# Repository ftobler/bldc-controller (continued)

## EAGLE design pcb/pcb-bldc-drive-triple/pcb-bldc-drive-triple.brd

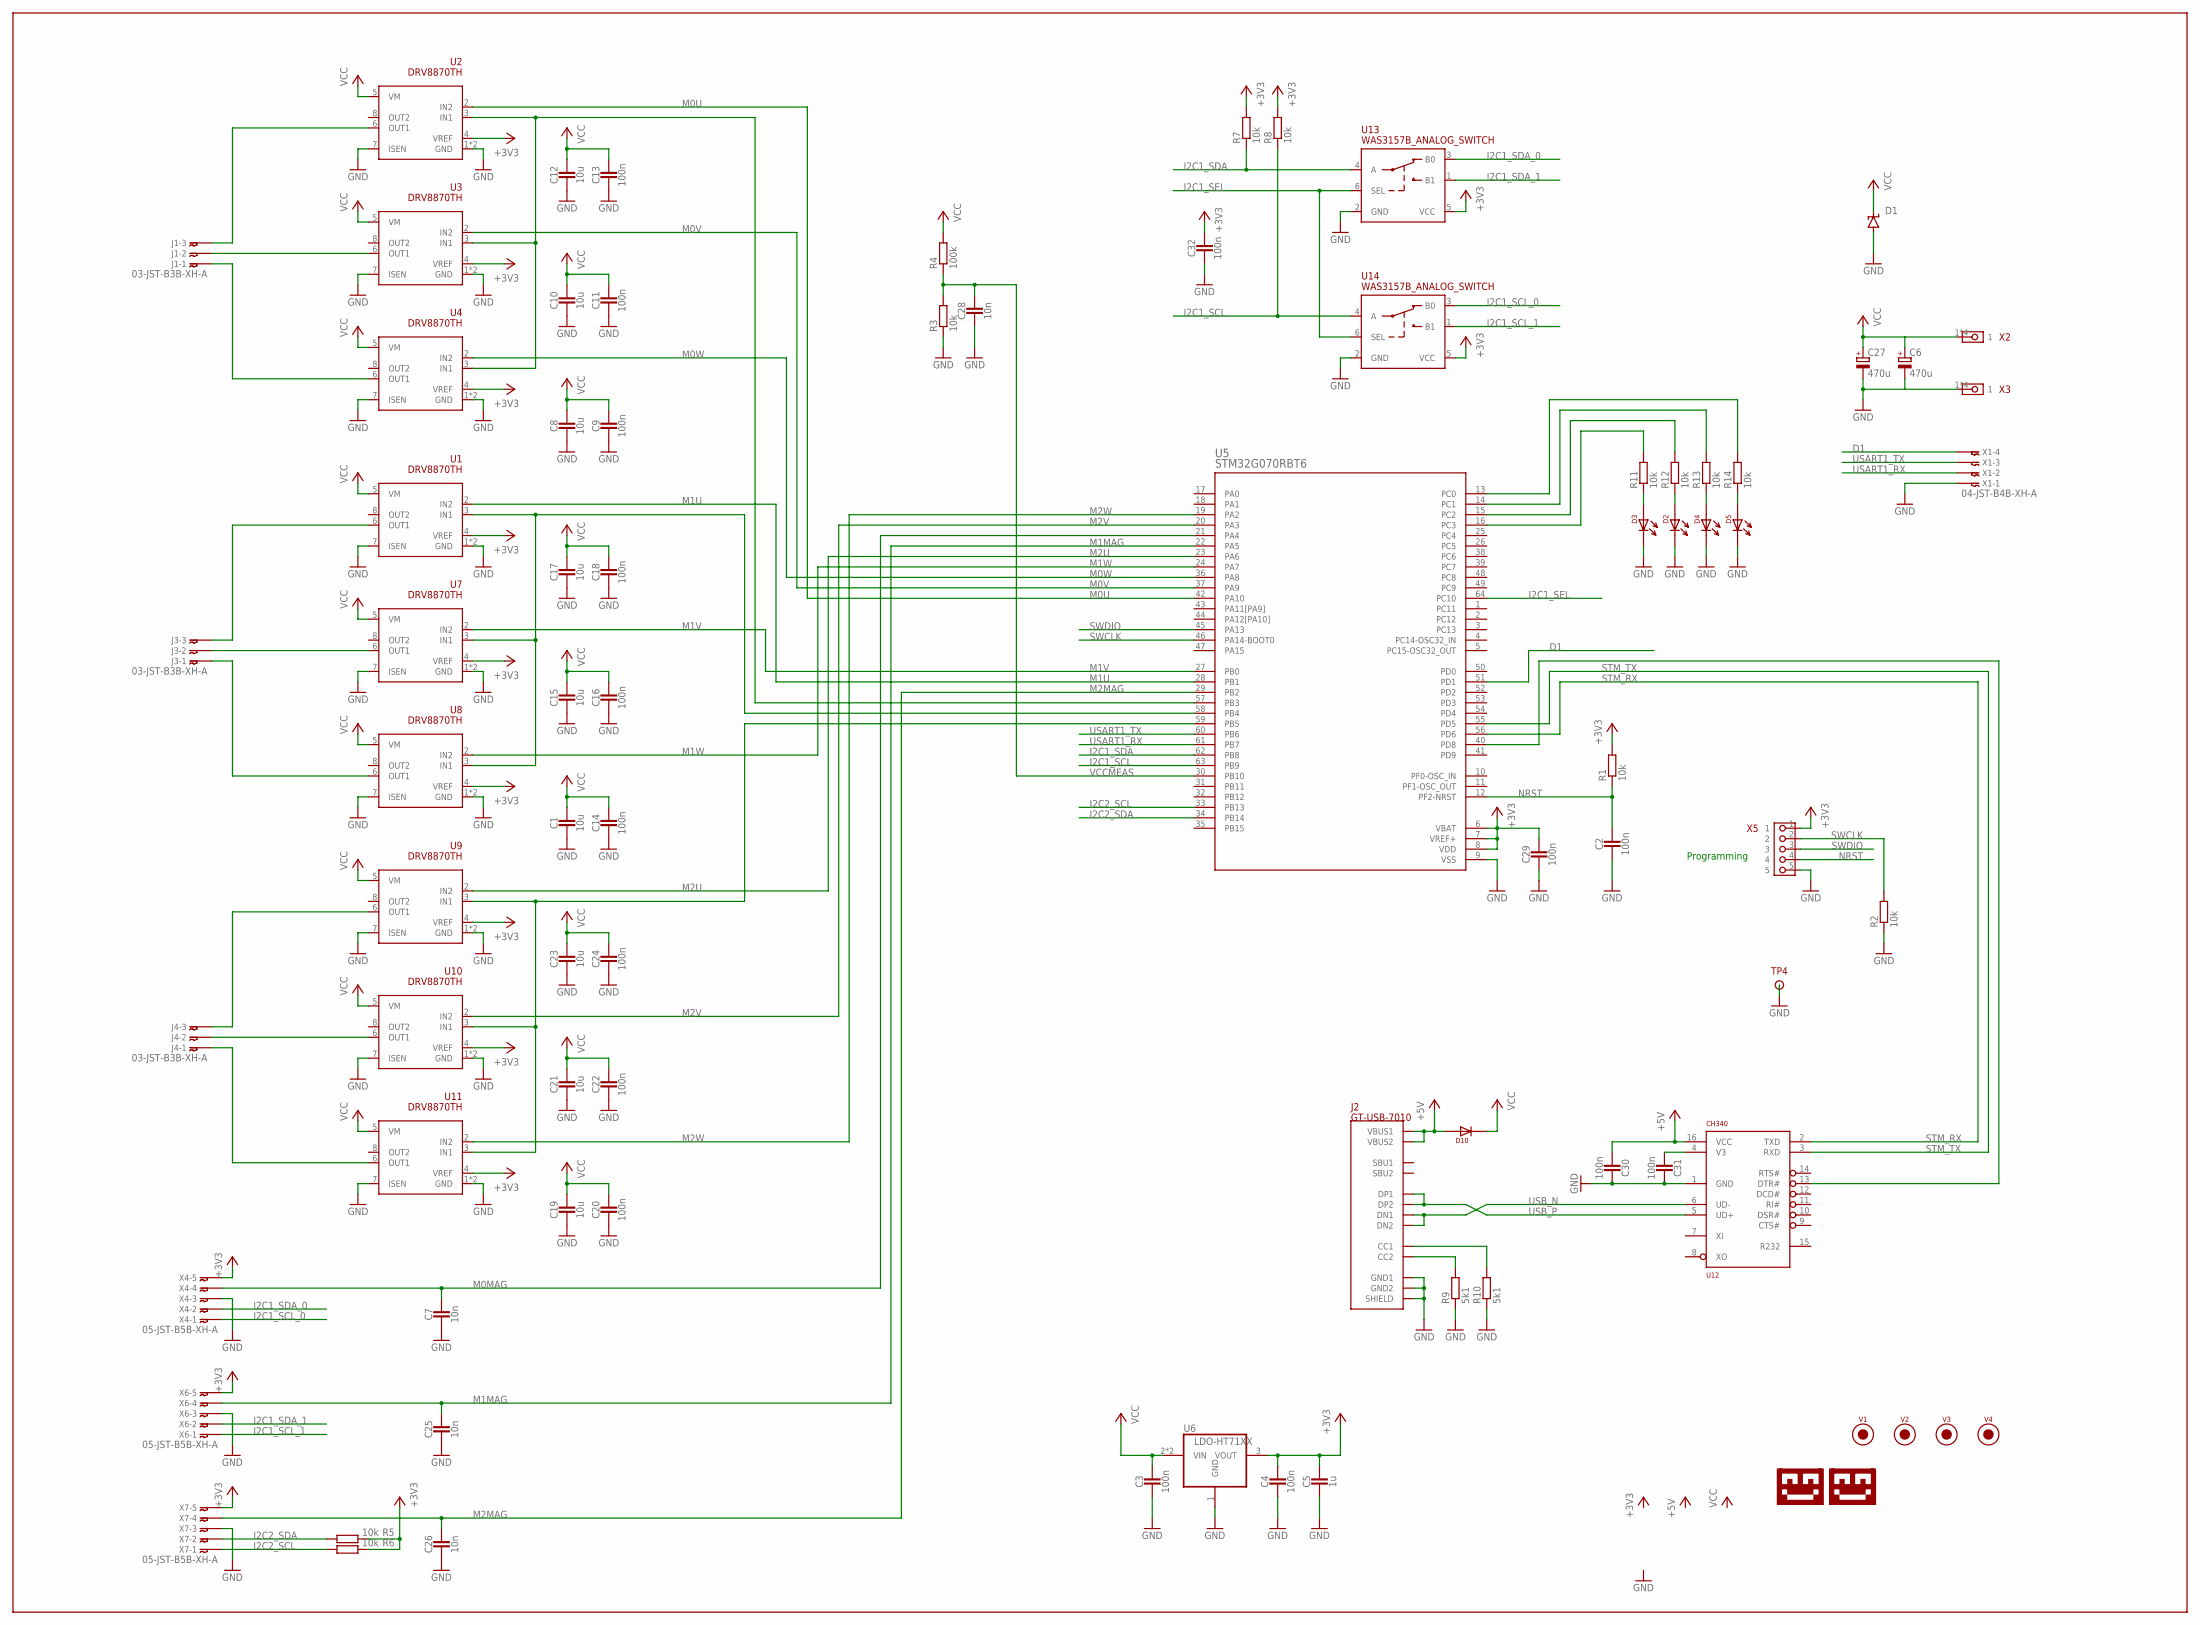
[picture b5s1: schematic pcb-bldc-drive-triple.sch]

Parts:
C1, C8, C10, C12, C15, C17, C19, C21, C23: 10u; 1206_CAP
C2, C3, C4, C9, C11, C13, C14, C16, C18, C20, C22, C24, C29, C30, C31, C32: 100n; 0603_CAP
C5: 1u; 0603_CAP
C6, C27: 470u; 153CLV-1010
C7, C25, C26, C28: 10n; 0603_CAP
D1: SUPPRESSOR-SMBJ; SMBJ
D2, D3, D4, D5: LED-0805; 0805-DOT
D10: DIODE-1206; 1206-DOT
J1, J3, J4: 03-JST-B3B-XH-A; B3B-XH
J2: GT-USB-7010
R1, R2, R3, R5, R6, R7, R8, R11, R12, R13, R14: 10k; 0603-RES
R4: 100k; 0603-RES
R9, R10: 5k1; 0603-RES
TP4: TESTPIN1MM; PIN-SMD-1X1-TEST_1M0
U1, U2, U3, U4, U7, U8, U9, U10, U11: DRV8870TH; SOIC-8-THERM
U5: STM32G070RBT6; LQFP-64
U6: LDO-HT71XX; SOT-89
U12: CH340; SOIC-16
U13, U14: WAS3157B_ANALOG_SWITCH; SOT323-6
U$1: LOGO-TOBENG-1MM-FINISH; TOBENG-1MM-FINISH
U$2: LOGO-TOBENG-4MM-MASK; TOBENG-4MM-MASK
V1, V2, V3, V4: FIDUCIAL2MM; FIDUCIAL_2MM
X1: 04-JST-B4B-XH-A; B4B-XH
X2, X3: PIN_1X1WELDINGTERMINAL; XFCNTS34031
X4, X6, X7: 05-JST-B5B-XH-A; B5B-XH
X5: PIN_5X1HD; PIN_5X1_HD

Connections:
+3V3: C4.1, C5.1, C29.1, C32.1, R1.2, R5.1, R6.1, R7.2, R8.2, U1.4 (VREF), U2.4 (VREF), U3.4 (VREF), U4.4 (VREF), U5.6 (VBAT), U5.7 (VREF+), U5.8 (VDD), U6.3 (VOUT), U7.4 (VREF), U8.4 (VREF), U9.4 (VREF), U10.4 (VREF), U11.4 (VREF), U13.5 (VCC), U14.5 (VCC), X4.P$5, X5.1, X6.P$5, X7.P$5
+5V: C30.2, D10.1, J2.A4B9 (VBUS1), J2.B4A9 (VBUS2), U12.16 (VCC)
D1: U5.51 (PD1), X1.P$4
GND: C1.2, C2.2, C3.2, C4.2, C5.2, C6.-, C7.2, C8.2, C9.2, C10.2, C11.2, C12.2, C13.2, C14.2, C15.2, C16.2, C17.2, C18.2, C19.2, C20.2, C21.2, C22.2, C23.2, C24.2, C25.2, C26.2, C27.-, C28.2, C29.2, C30.1, C31.1, C32.2, D1.A, D2.2, D3.2, D4.2, D5.2, J2.13 (SHIELD), J2.14 (SHIELD), J2.15 (SHIELD), J2.16 (SHIELD), J2.A1B12 (GND1), J2.B1A12 (GND2), R2.1, R3.1, R9.1, R10.1, TP4.1, U1.1 (GND), U1.7 (ISEN), U1.9 (GND), U2.1 (GND), U2.7 (ISEN), U2.9 (GND), U3.1 (GND), U3.7 (ISEN), U3.9 (GND), U4.1 (GND), U4.7 (ISEN), U4.9 (GND), U5.9 (VSS), U6.1 (GND), U7.1 (GND), U7.7 (ISEN), U7.9 (GND), U8.1 (GND), U8.7 (ISEN), U8.9 (GND), U9.1 (GND), U9.7 (ISEN), U9.9 (GND), U10.1 (GND), U10.7 (ISEN), U10.9 (GND), U11.1 (GND), U11.7 (ISEN), U11.9 (GND), U12.1 (GND), U13.2 (GND), U14.2 (GND), X1.P$1, X3.1, X3.2, X3.3, X3.4, X4.P$3, X5.5, X6.P$3, X7.P$3
I2C1_SCL: R8.1, U5.63 (PB9), U14.4 (A)
I2C1_SCL_0: U14.3 (B0), X4.P$1
I2C1_SCL_1: U14.1 (B1), X6.P$1
I2C1_SDA: R7.1, U5.62 (PB8), U13.4 (A)
I2C1_SDA_0: U13.3 (B0), X4.P$2
I2C1_SDA_1: U13.1 (B1), X6.P$2
I2C1_SEL: U5.64 (PC10), U13.6 (SEL), U14.6 (SEL)
I2C2_SCL: R6.2, U5.33 (PB13), X7.P$1
I2C2_SDA: R5.2, U5.34 (PB14), X7.P$2
M0MAG: C7.1, U5.21 (PA4), X4.P$4
M0U: U2.2 (IN2), U5.42 (PA10)
M0V: U3.2 (IN2), U5.37 (PA9)
M0W: U4.2 (IN2), U5.36 (PA8)
M1MAG: C25.1, U5.22 (PA5), X6.P$4
M1U: U1.2 (IN2), U5.28 (PB1)
M1V: U5.27 (PB0), U7.2 (IN2)
M1W: U5.24 (PA7), U8.2 (IN2)
M2MAG: C26.1, U5.29 (PB2), X7.P$4
M2U: U5.23 (PA6), U9.2 (IN2)
M2V: U5.20 (PA3), U10.2 (IN2)
M2W: U5.19 (PA2), U11.2 (IN2)
unnamed: J2.B5 (CC2), R9.2
unnamed: J2.A5 (CC1), R10.2
unnamed: J1.P$2, U3.6 (OUT1)
unnamed: J1.P$3, U2.6 (OUT1)
unnamed: C31.2, U12.4 (V3)
unnamed: J3.P$3, U1.6 (OUT1)
unnamed: J1.P$1, U4.6 (OUT1)
unnamed: D3.1, R11.1
unnamed: J3.P$2, U7.6 (OUT1)
unnamed: J3.P$1, U8.6 (OUT1)
unnamed: U5.59 (PB5), U9.3 (IN1), U10.3 (IN1), U11.3 (IN1)
unnamed: U1.3 (IN1), U5.58 (PB4), U7.3 (IN1), U8.3 (IN1)
unnamed: J4.P$3, U9.6 (OUT1)
unnamed: U2.3 (IN1), U3.3 (IN1), U4.3 (IN1), U5.57 (PB3)
unnamed: J4.P$2, U10.6 (OUT1)
unnamed: J4.P$1, U11.6 (OUT1)
unnamed: D2.1, R12.1
unnamed: D4.1, R13.1
unnamed: D5.1, R14.1
unnamed: R14.2, U5.13 (PC0)
unnamed: R13.2, U5.14 (PC1)
unnamed: R12.2, U5.15 (PC2)
unnamed: R11.2, U5.16 (PC3)
unnamed: U5.40 (PD8), U12.13 (DTR#)
NRST: C2.1, R1.1, U5.12 (PF2-NRST), X5.4
STM_RX: U5.56 (PD6), U12.2 (TXD)
STM_TX: U5.55 (PD5), U12.3 (RXD)
SWCLK: R2.2, U5.46 (PA14-BOOT0), X5.2
SWDIO: U5.45 (PA13), X5.3
USART1_RX: U5.61 (PB7), X1.P$2
USART1_TX: U5.60 (PB6), X1.P$3
USB_N: J2.A7 (DN1), J2.B7 (DN2), U12.6 (UD-)
USB_P: J2.A6 (DP1), J2.B6 (DP2), U12.5 (UD+)
VCC: C1.1, C3.1, C6.+, C8.1, C9.1, C10.1, C11.1, C12.1, C13.1, C14.1, C15.1, C16.1, C17.1, C18.1, C19.1, C20.1, C21.1, C22.1, C23.1, C24.1, C27.+, D1.C, D10.2, R4.2, U1.5 (VM), U2.5 (VM), U3.5 (VM), U4.5 (VM), U6.2 (VIN), U6.2@1 (VIN), U7.5 (VM), U8.5 (VM), U9.5 (VM), U10.5 (VM), U11.5 (VM), X2.1, X2.2, X2.3, X2.4
VCCMEAS: C28.1, R3.2, R4.1, U5.30 (PB10)

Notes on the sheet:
Programming

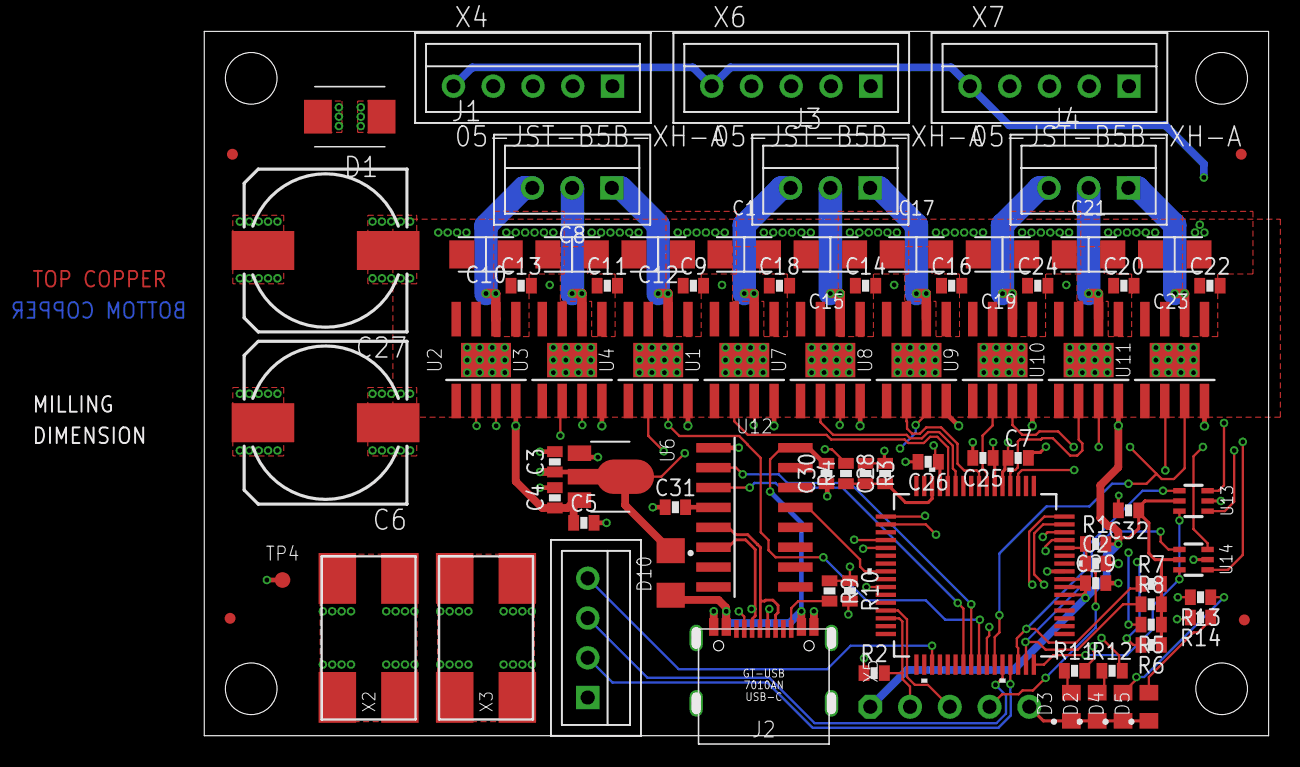
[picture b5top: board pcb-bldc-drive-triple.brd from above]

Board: 4 copper layers, 68.0 x 45.0 mm, 84 parts (1 on the bottom side), 60 nets.

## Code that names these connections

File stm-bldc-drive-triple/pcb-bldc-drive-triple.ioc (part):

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Mcu.Name=STM32G070RBTx
Mcu.Package=LQFP64
Mcu.UserName=STM32G070RBTx
PA10.Signal=S_TIM1_CH3
PA11\ [PA9].Signal=S_TIM1_CH4
PA13.Mode=Serial_Wire
PA13.Signal=SYS_SWDIO
PA14-BOOT0.Mode=Serial_Wire
PA14-BOOT0.Signal=SYS_SWCLK
PA2.Signal=S_TIM15_CH1
PA3.Signal=S_TIM15_CH2
PA4.Mode=IN4
PA4.Signal=ADC1_IN4
PA5.Mode=IN5
PA5.Signal=ADC1_IN5
PA6.Signal=S_TIM3_CH1
PA7.Signal=S_TIM3_CH2
PA8.Signal=S_TIM1_CH1
PA9.Signal=S_TIM1_CH2
PB0.Signal=S_TIM3_CH3
PB1.Signal=S_TIM3_CH4
PB10.Mode=IN11
PB10.Signal=ADC1_IN11
PB13.Mode=I2C
PB13.Signal=I2C2_SCL
PB14.Mode=I2C
PB14.Signal=I2C2_SDA
PB2.Mode=IN10
PB2.Signal=ADC1_IN10
PB3.GPIOParameters=GPIO_Label
PB3.GPIO_Label=ENABLE_M3
PB3.Signal=GPIO_Output
PB4.GPIOParameters=GPIO_Label
PB4.GPIO_Label=ENABLE_M2
PB4.Signal=GPIO_Output
PB5.GPIOParameters=GPIO_Label
PB5.GPIO_Label=ENABLE_M1
PB5.Signal=GPIO_Output
PB6.Mode=Asynchronous
PB6.Signal=USART1_TX
PB7.Mode=Asynchronous
PB7.Signal=USART1_RX
PB8.Mode=I2C
PB8.Signal=I2C1_SCL
PB9.Mode=I2C
PB9.Signal=I2C1_SDA
PC0.GPIOParameters=GPIO_Label
PC0.GPIO_Label=LED1
PC0.Signal=GPIO_Output
PC1.GPIOParameters=GPIO_Label
PC1.GPIO_Label=LED2
PC1.Signal=GPIO_Output
PC10.GPIOParameters=GPIO_Label
PC10.GPIO_Label=I2C1_SEL
PC10.Signal=GPIO_Output
PC2.GPIOParameters=GPIO_Label
PC2.GPIO_Label=LED3
PC2.Signal=GPIO_Output
PC3.GPIOParameters=GPIO_Label
PC3.GPIO_Label=LED4
PC3.Signal=GPIO_Output
PD5.Mode=Asynchronous
PD5.Signal=USART2_TX
PD6.Mode=Asynchronous
PD6.Signal=USART2_RX
PD8.GPIOParameters=GPIO_Label
PD8.GPIO_Label=DTR
PD8.Signal=GPIO_Input
RCC.HSE_VALUE=8000000
RCC.SYSCLKFreq_VALUE=64000000
RCC.SYSCLKSource=RCC_SYSCLKSOURCE_PLLCLK
board=custom

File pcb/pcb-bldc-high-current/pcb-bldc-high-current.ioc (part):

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Mcu.Name=STM32G070RBTx
Mcu.Package=LQFP64
Mcu.UserName=STM32G070RBTx
PA10.Signal=S_TIM1_CH3
PA13.Mode=Serial_Wire
PA13.Signal=SYS_SWDIO
PA14-BOOT0.Mode=Serial_Wire
PA14-BOOT0.Signal=SYS_SWCLK
PA7.Mode=Output Compare1 CH1 CH1N
PA7.Signal=TIM1_CH1N
PA8.Signal=S_TIM1_CH1
PA9.Signal=S_TIM1_CH2
PB0.Mode=Output Compare2 CH2 CH2N
PB0.Signal=TIM1_CH2N
PB1.Mode=Output Compare3 CH3 CH3N
PB1.Signal=TIM1_CH3N
PB6.Mode=Asynchronous
PB6.Signal=USART1_TX
PB7.Mode=Asynchronous
PB7.Signal=USART1_RX
PD5.Mode=Asynchronous
PD5.Signal=USART2_TX
PD6.Mode=Asynchronous
PD6.Signal=USART2_RX
PD8.Mode=Asynchronous
PD8.Signal=USART3_TX
PD9.Mode=Asynchronous
PD9.Signal=USART3_RX
PF0-OSC_IN\ (PF0).Mode=HSE-External-Oscillator
PF0-OSC_IN\ (PF0).Signal=RCC_OSC_IN
PF1-OSC_OUT\ (PF1).Mode=HSE-External-Oscillator
PF1-OSC_OUT\ (PF1).Signal=RCC_OSC_OUT
RCC.HSE_VALUE=8000000
RCC.SYSCLKFreq_VALUE=16000000
board=custom

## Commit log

2024-05-10 initial
2024-05-10 add dc motor driver
2024-05-10 stm32 project DC controller
2024-05-10 speed calculation (qualitative)
2024-05-10 triple drive project
2024-05-11 external motor class, oversampling
2024-05-11 position controller, automatic calibration
2024-05-12 working on 3 motors
2024-05-12 task scheduling, custom sine, demo
2024-05-12 fix tasks and startup
2024-05-12 start only when all motors are done with calibration
2024-05-12 control loop and improved homing in calibration
2024-05-14 optimization
2024-05-23 control loop (and calibration) for robot (not working well)
2024-05-23 more stable controls
2024-05-23 even better control loops
2024-05-25 inverse kinematics and demo
2024-05-25 speed
2024-06-11 Sensorless pcb variant 1. Currently abandoned.
2024-06-11 pcb sensorless 2 pcb release
2024-06-11 tweaks for better operation
2024-06-11 readme
2024-06-11 first version
2024-06-11 2 rs485 drivers
2024-06-11 pcb release high current
